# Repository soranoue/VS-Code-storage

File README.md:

# soranoue的暂存仓库

## 仓库介绍
    本仓库主要用于存放作者soranoue的部分学习代码,同时会用于测试学习
    有想要的代码可以自行取用(能帮忙Star下最好)

    目前包含的内容有:
    - 简单的README文件
    - 简单的C语言程序
    - 简单的Cpp程序(基于大学教材课后题)
    - 新建的Python文件夹(学习Python用)

    日后可能加入的内容有:
    - 8051内核单片机程序
    - ARM内核单片机程序
    - Altera FPGA CPLD
    - Xilinx FPGA SOC

## 关于作者
    soranoue,电子爱好者,偶尔也会捣鼓一些复古设备
    名称来源于日语'空の上'
    目前没有考取任何证书
    2022年起就读于中北大学(上兰帝国理工大学)(bushi)

#### 此README.md写于2025/3/15,测试用

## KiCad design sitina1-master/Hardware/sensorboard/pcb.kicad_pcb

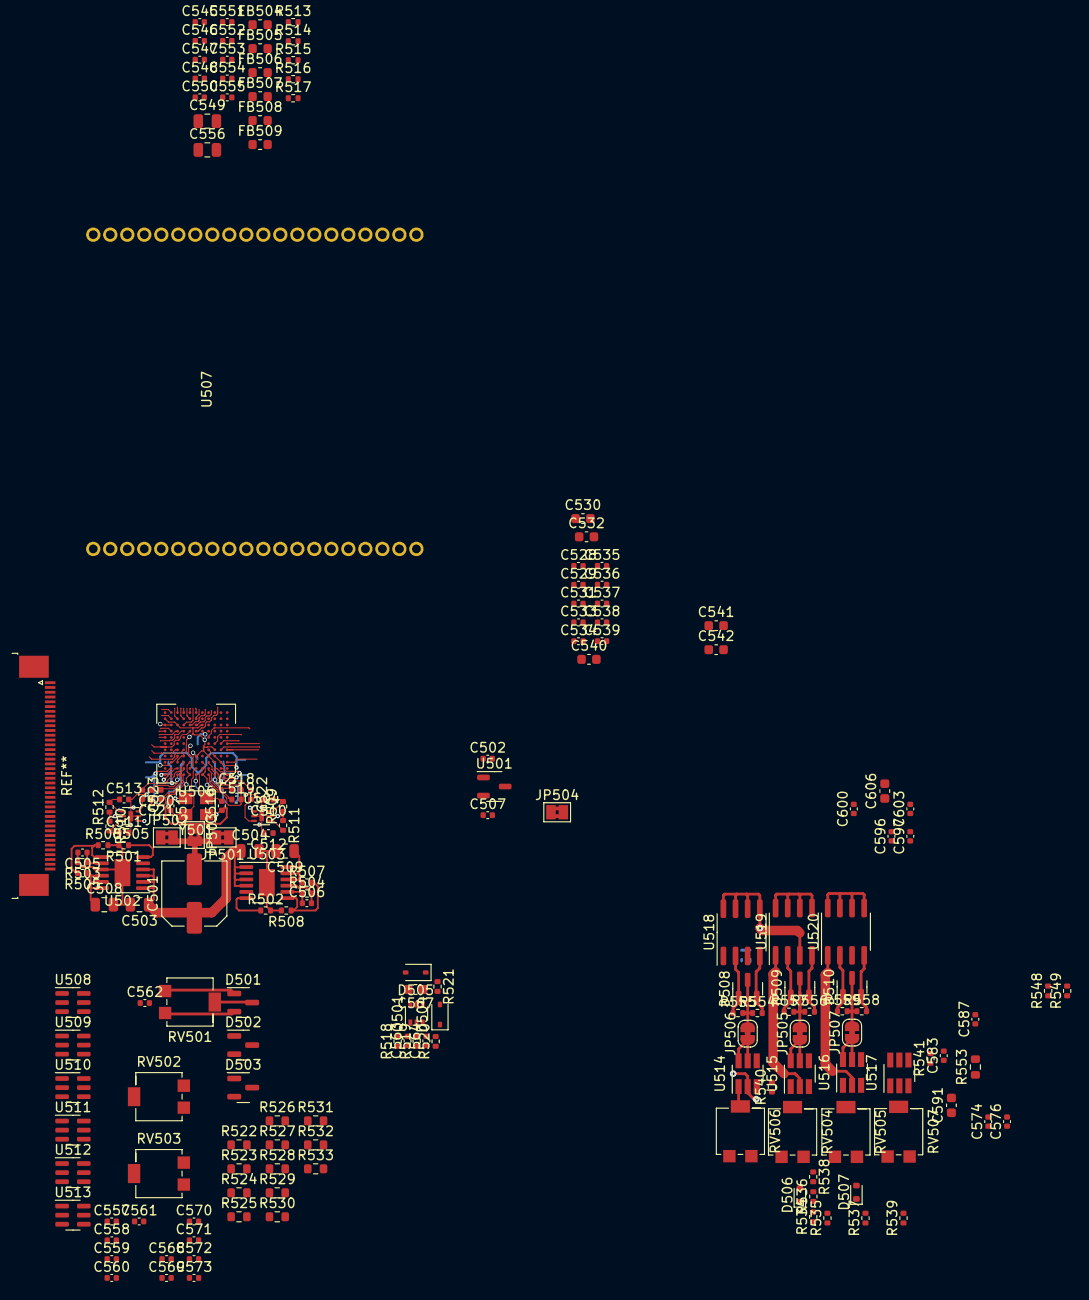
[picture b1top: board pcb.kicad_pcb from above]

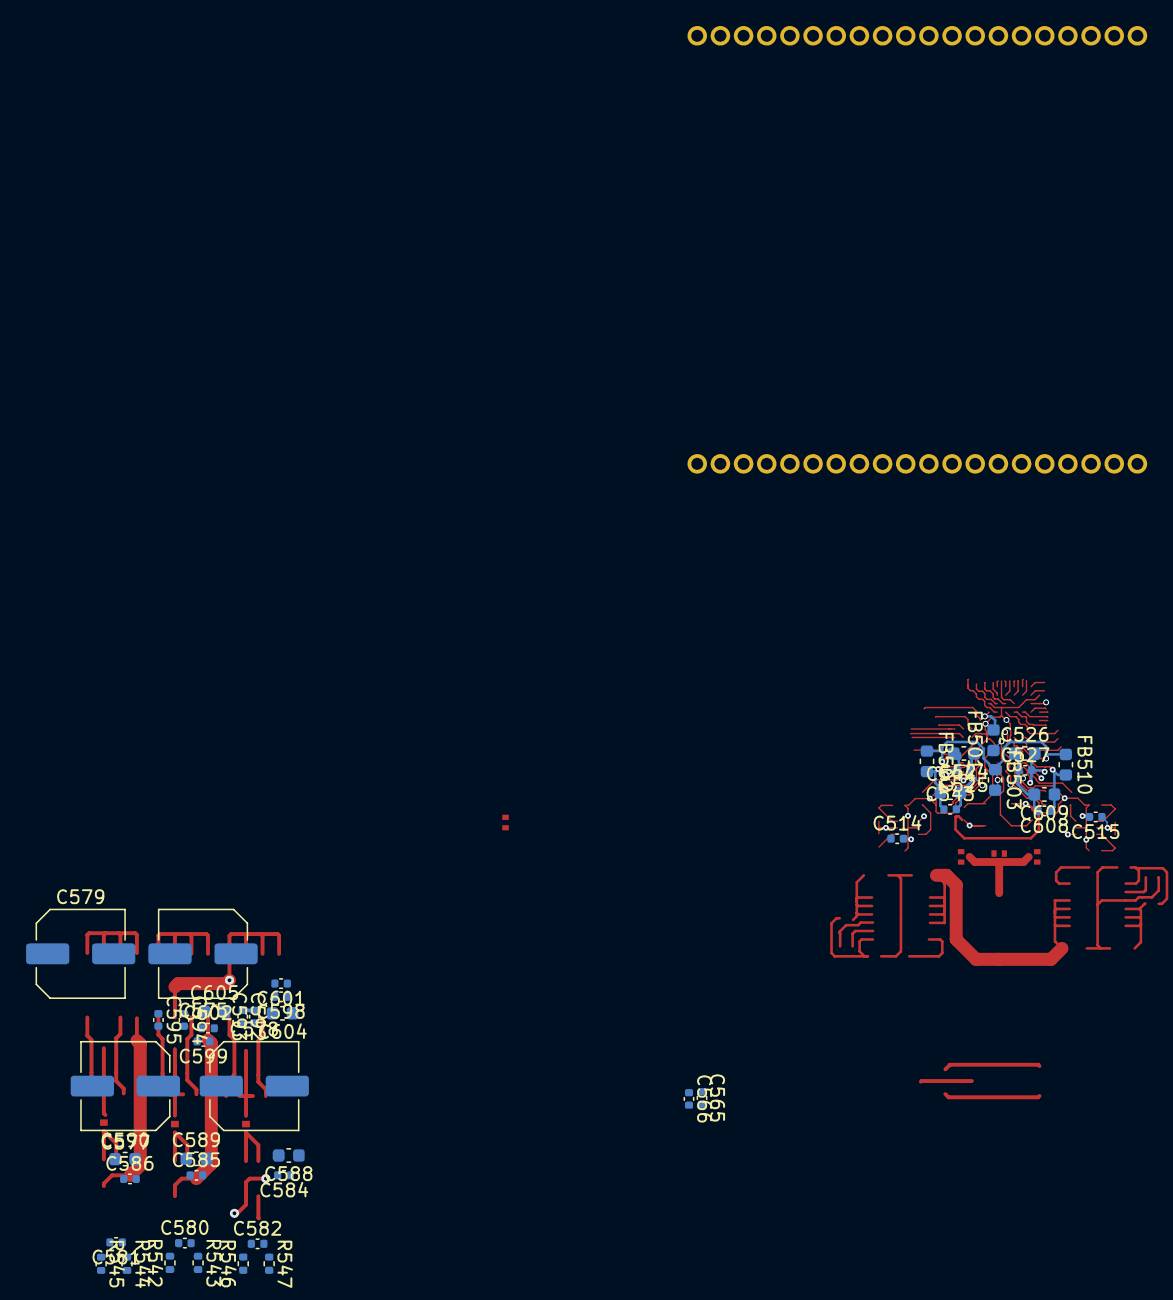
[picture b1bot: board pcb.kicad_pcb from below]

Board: 4 copper layers, 220 parts (45 on the bottom side), 129 nets.

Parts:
C501, C575, C577, C578, C579: 470uF; C_Elec_6.3x7.7
C502, C507, C518, C519, C520, C521, C574, C576, C601, C602, C603: 1uF; C_0402_1005Metric
C503, C504: 10uF; C_0805_2012Metric
C505, C506, C547, C548: 4.7uF; C_0402_1005Metric
C508, C509, C549, C556: 22uF 25V; C_0805_2012Metric
C510, C511, C512, C513, C514, C515, C522, C523, C525, C527, C528, C529, C531, C533, C534, C535, C536, C537, C538, C539, C543, C545, C546, C550, C551, C552, C553, C554, C555, C560, C561, C562, C563, C564, C565, C566, C568, C569, C570, C571, C572, C573, C580, C581, C582, C583, C584, C585, C586, C587, C598, C599, C600, C608: 100nF; C_0402_1005Metric
C516, C517: 18pF; C_0402_1005Metric
C524, C526, C530, C532, C540, C542, C544, C588, C589, C590, C591, C604, C605, C606, C609: 10uF; C_0603_1608Metric
C541: 100nF; C_0603_1608Metric
C557, C558, C559: 10uF; C_0402_1005Metric
C567: 1uF 25V; C_0603_1608Metric
C592, C593, C594, C595, C596, C597: 1nF; C_0402_1005Metric
D501, D502, D503, D508, D509, D510: BAT54S; SOT-23
D504, D505: B0540W; D_SOD-323
D506, D507: 1N4148; D_SOD-523
FB501, FB502, FB503, FB504, FB505, FB506, FB507, FB508, FB509, FB510: FerriteBead; L_0603_1608Metric
JP501, JP502, JP503, JP504: SolderJumper_2_Bridged; SolderJumper-2_P1.3mm_Bridged2Bar_Pad1.0x1.5mm
JP505, JP506, JP507: Jumper_2_Bridged; SolderJumper-2_P1.3mm_Bridged_RoundedPad1.0x1.5mm
Q501: BC847BPN; SOT-363_SC-70-6
R501, R502: 249R; R_0402_1005Metric
R503, R504: 30.1K; R_0402_1005Metric
R505, R507, R516: 270K 1%; R_0402_1005Metric
R506, R508: 22K 1%; R_0402_1005Metric
R509, R510: 49.9K 1%; R_0402_1005Metric
R511, R512, R513: 200K 1%; R_0402_1005Metric
R514: 120K 1%; R_0402_1005Metric
R515: 82K 1%; R_0402_1005Metric
R517: 7.5; R_0402_1005Metric
R518, R519, R521: 10K; R_0402_1005Metric
R520: 0; R_0402_1005Metric
R522, R523, R524, R525, R526, R527, R528, R529, R530, R531, R532, R533: 0.1; R_0603_1608Metric
R534, R535, R540, R541: 22; R_0402_1005Metric
R536, R537, R538, R539, R542, R543, R544, R545, R546, R547, R548, R549: 5k; R_0402_1005Metric
R553: Short; R_0603_1608Metric
R554, R555, R556, R557, R558, R559: 220; R_0402_1005Metric
RV501, RV502, RV503: 50K; Potentiometer_Bourns_3214G_Horizontal
RV504, RV505, RV506, RV507: 10K; Potentiometer_Bourns_3214G_Horizontal
U501: XC6206P152MR; SOT-23-3
U502, U503: LT3045xMSE; MSOP-12-1EP_3x4mm_P0.65mm_EP1.65x2.85mm
U504, U505: ADA4800; DFN-6-1EP_1.6x1.6mm_P0.5mm_EP0.5x1.05mm
U506: AD9990; BGA-112_11x11_8.0x8.0mm
U507: KAI-1100x; KAI-1100X
U508, U509, U510, U511, U512, U513: 74HC2G17; SC-74-6_1.5x2.9mm_P0.95mm
U514, U515, U516, U517: 1EDN7550B; SOT-23-6_Handsoldering
U518, U519, U520: IRF9389/7309; SOIC-8_3.9x4.9mm_P1.27mm
Y501: 28MHz; Crystal_SMD_3225-4Pin_3.2x2.5mm

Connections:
+1V5: C558.2, C568.1, D502.2 (K), RV502.1, U508.5 (VCC)
+1V8: C507.1, C528.2, FB501.2, U501.2 (VO), U506.H5 (DVDD)
+2V: C569.1, C570.1, C571.1, C572.1, C573.1, D501.2 (K), D503.2 (K), RV501.1, RV503.1, U509.5 (VCC), U510.5 (VCC), U511.5 (VCC), U512.5 (VCC), U513.5 (VCC)
+3V3: C502.1, C530.2, C531.2, C532.2, C533.2, C534.2, C535.2, C536.2, C537.2, C538.2, C539.2, C540.2, C559.2, C574.2, FB502.1, FB503.1, FB510.1, R546.2, R548.2, U501.3 (VI), U506.C2 (RGVDD_A), U506.C10 (RGVDD_B), U506.D3 (HVDD_A), U506.D9 (HVDD_B), U506.E4 (XVVDD), U506.J10 (DRVDD), U506.J11 (IOVDD)
+5V: C579.1, C587.2, C591.2, U517.4 (VDD)
+8V: C578.1, C584.2, C588.2, C598.2, C601.2, C604.2, U514.4 (VDD), U518.3 (SP)
+15VL: C508.1, C515.1, C546.1, FB504.1, R505.1, R510.1, R512.1, R515.1, U502.10 (OUTS), U502.11 (OUT), U502.12 (OUT), U505.5 (VCC)
+15VR: C509.1, C514.1, FB509.1, R507.1, R509.1, R511.1, U503.10 (OUTS), U503.11 (OUT), U503.12 (OUT), U504.5 (VCC)
+16V: C501.1, C503.1, C504.1, C565.2, Q501.4 (E2), R518.1, U502.1 (IN), U502.2 (IN), U502.3 (IN), U502.4 (EN/UV), U503.1 (IN), U503.2 (IN), U503.3 (IN), U503.4 (EN/UV)
-3V5: C557.1, C568.2, D502.1 (A), RV502.3, U508.2 (GND)
-4V: C545.2, C569.2, C570.2, C571.2, C572.2, C573.2, C576.1, C580.1, C581.1, D501.1 (A), D503.1 (A), R514.2, R543.1, R545.1, RV501.3, RV503.3, U509.2 (GND), U510.2 (GND), U511.2 (GND), U512.2 (GND), U513.2 (GND)
-9V: C575.2, C577.2, C585.1, C586.1, C587.1, C589.1, C590.1, C591.1, C599.2, C600.2, C602.1, C603.1, C605.1, C606.1, R517.1, R538.1, R539.1, U515.2 (GND), U516.2 (GND), U517.2 (GND), U519.1 (SN), U520.1 (SN)
-15V: C566.1, D504.2 (A), R520.2
/afe/AVDDA: C524.2, C525.2, U506.A1 (LDOOUT_A), U506.C4 (AVDD_A)
/afe/AVDDB: C526.2, C527.2, U506.A11 (LDOOUT_B), U506.C8 (AVDD_B)
/afe/AVSS: C516.1, C517.1, C541.2, C542.2, JP503.1 (A), U506.B3 (LDOVSS_A), U506.B9 (LDOVSS_B), Y501.2, Y501.4
/afe/AVSSA: C510.2, C512.2, C514.2, C518.2, C519.2, C524.1, C525.1, C543.2, C544.2, JP501.1 (A), U504.2 (VEE), U504.7 (EPAD), U506.A3 (AVSS_A), U506.A5 (AVSS_A), U506.C5 (AVSS_A)
/afe/AVSSB: C511.2, C513.2, C515.2, C520.2, C521.2, C526.1, C527.1, C608.2, C609.2, JP502.1 (A), U505.2 (VEE), U505.7 (EPAD), U506.A7 (AVSS_B), U506.A9 (AVSS_B), U506.C7 (AVSS_B)
/afe/CLI: C516.2, U506.B5 (CLI), Y501.1
/afe/CLO: C517.2, U506.B6 (CLO), Y501.3
/afe/DVSS: C528.1, C529.1, C530.1, C531.1, C532.1, C533.1, C534.1, C535.1, C536.1, C537.1, C538.1, C539.1, C540.1, JP504.1 (A), U506.C3 (RGVSS_A), U506.C6 (TCVSS), U506.C9 (RGVSS_B), U506.D4 (HVSS_A), U506.D6 (TCVSS), U506.D8 (HVSS_B), U506.E3 (XVVSS), U506.J5 (DVSS), U506.J9 (DRVSS), U506.K11 (IOVSS)
/ccd/VDDL: C549.1, C552.1, FB504.2, U507.3 (VDDL)
/ccd/VDDR: C555.1, C556.1, FB509.2, U507.18 (VDDR)
/ccd/VOD: C547.2, FB505.1, FB506.1, R513.2, R514.1
/ccd/VOGL: C553.1, FB506.2, U507.40 (OGL)
/ccd/VOGR: C554.1, FB505.2, U507.21 (OGR)
/ccd/VRDL: C550.1, FB508.2, U507.38 (VRDL)
/ccd/VRDR: C551.1, FB507.2, U507.23 (VRDR)
/ccd_driver/H1BINL: R524.1, U509.6 (1Y)
/ccd_driver/H1BINR: R525.1, U509.4 (2Y)
/ccd_driver/H1BL: R528.1, U511.6 (1Y)
/ccd_driver/H1BR: R531.1, U512.4 (2Y)
/ccd_driver/H1S: C561.2, D503.3 (COM), RV503.2, U509.1 (1A), U509.3 (2A), U511.1 (1A), U512.3 (2A), U513.1 (1A)
/ccd_driver/H1SL: R527.1, U510.4 (2Y)
/ccd_driver/H1SR: R532.1, U513.6 (1Y)
/ccd_driver/H2BL: R529.1, U511.4 (2Y)
/ccd_driver/H2BR: R530.1, U512.6 (1Y)
/ccd_driver/H2S: C562.2, D501.3 (COM), RV501.2, U510.1 (1A), U510.3 (2A), U511.3 (2A), U512.1 (1A), U513.3 (2A)
/ccd_driver/H2SL: R526.1, U510.6 (1Y)
/ccd_driver/H2SR: R533.1, U513.4 (2Y)
/ccd_driver/RGS: C560.2, D502.3 (COM), RV502.2, U508.1 (1A), U508.3 (2A)
/ccd_driver/RL: R522.1, U508.6 (1Y)
/ccd_driver/RR: R523.1, U508.4 (2Y)
/ccd_driver_v/V2S: D509.3 (COM), D510.3 (COM), JP505.2 (B), JP507.2 (B), R556.1, R557.2, R558.1, R559.2
/ccd_driver_v/V23: D508.3 (COM), JP506.2 (B), R554.1, R555.2
AFE_FDG: R541.1, U506.G4 (XV4)
AFE_H1: C561.1, U506.E1 (H1A)
AFE_H2: C562.1, U506.E2 (H2A)
AFE_RG: C560.1, U506.C1 (HL_A)
AFE_STROBE: C563.2, C564.2, U506.G11 (GPO1)
AFE_V1: R535.1, U506.F3 (XV1)
AFE_V2: R534.1, U506.F2 (XV2)
AFE_V23: R540.1, U506.F1 (XV3)
CCDIN_L: U505.1 (IN), U507.2 (VOUTL)
CCDIN_R: U504.1 (IN), U507.19 (VOUTR)
FDG_CCD: R553.1, U507.22 (FD), U507.39 (FD)
GND: C501.2, C502.2, C503.2, C504.2, C505.2, C506.2, C507.2, C508.2, C509.2, C545.1, C546.2, C547.1, C548.2, C549.2, C550.2, C551.2, C552.2, C553.2, C554.2, C555.2, C556.2, C557.2, C558.1, C559.1, C565.1, C566.2, C574.1, C575.1, C576.2, C577.1, C578.2, C579.2, C582.1, C583.1, C584.1, C585.2, C586.2, C588.1, C589.2, C590.2, C598.1, C599.1, C600.1, C601.1, C602.2, C603.2, C604.1, C605.2, C606.2, D506.2 (A), D507.2 (A), JP501.2 (B), JP502.2 (B), JP503.2 (B), JP504.2 (B), R501.2, R502.2, R503.2, R504.2, R506.2, R508.2, R513.1, R516.2, R519.2, R521.2, R542.2, R544.2, R547.1, R549.1, U501.1 (GND), U502.9 (GND), U502.13 (GND), U503.9 (GND), U503.13 (GND), U507.4 (GND), U507.6 (GND), U507.15 (GND), U507.17 (GND), U507.26 (GND), U507.28 (GND), U507.29 (GND), U507.30 (GND), U507.31 (GND), U507.32 (GND), U507.33 (GND), U507.35 (GND), U514.2 (GND), U515.4 (VDD), U516.4 (VDD), U518.1 (SN), U520.3 (SP)
H1BINL_CCD: R524.2, U507.5 (H1BINL)
H1BINR_CCD: R525.2, U507.16 (H1BINR)
H1BL_CCD: R528.2, U507.9 (H1BL)
H1BR_CCD: R531.2, U507.12 (H1BR)
H1SL_CCD: R527.2, U507.8 (H1SL)
H1SR_CCD: R532.2, U507.13 (H1SR)
H2BL_CCD: R529.2, U507.10 (H2BL)
H2BR_CCD: R530.2, U507.11 (H2BR)
H2SL_CCD: R526.2, U507.7 (H2SL)
H2SR_CCD: R533.2, U507.14 (H2SR)
unnamed: C548.1, FB507.1, FB508.1, R515.2, R516.1
unnamed: C564.1, D504.1 (K), Q501.2 (B1), R519.1
unnamed: D506.1 (K), R534.2, R536.1
unnamed: D507.1 (K), R535.2, R537.1
unnamed: C593.1, D508.1 (A), R555.1, U518.2 (GN)
unnamed: C592.2, D508.2 (K), R554.2, U518.4 (GP)
unnamed: C595.1, D509.1 (A), R557.1, U519.2 (GN)
unnamed: C594.2, D509.2 (K), R556.2, U519.4 (GP)
unnamed: C597.1, D510.1 (A), R559.1, U520.2 (GN)
unnamed: C596.2, D510.2 (K), R558.2, U520.4 (GP)
unnamed: JP505.1 (A), U515.5 (OUT_SRC), U515.6 (OUT_SNK)
unnamed: JP506.1 (A), U514.5 (OUT_SRC), U514.6 (OUT_SNK)
unnamed: JP507.1 (A), U516.5 (OUT_SRC), U516.6 (OUT_SNK)
unnamed: C567.2, Q501.3 (C2), Q501.6 (C1)
unnamed: Q501.1 (E1), R520.1
unnamed: C563.1, Q501.5 (B2), R518.2
unnamed: R542.1, RV504.1
unnamed: R543.2, RV504.3
unnamed: R544.1, RV505.1
unnamed: R545.2, RV505.3
unnamed: R546.1, RV506.1
unnamed: R547.2, RV506.3
unnamed: R548.1, RV507.1
unnamed: R549.2, RV507.3
unnamed: R501.1, U502.6 (ILIM)
unnamed: R505.2, R506.1, U502.7 (PGFB)
unnamed: C505.1, R503.1, U502.8 (SET)
unnamed: R502.1, U503.6 (ILIM)
unnamed: R507.2, R508.1, U503.7 (PGFB)
unnamed: C506.1, R504.1, U503.8 (SET)
unnamed: C512.1, R511.2, U504.4 (IDRV)
unnamed: C510.1, R509.2, U504.6 (ISF)
unnamed: C522.2, U504.3 (OUT)
unnamed: C513.1, R512.2, U505.4 (IDRV)
unnamed: C511.1, R510.2, U505.6 (ISF)
unnamed: C523.2, U505.3 (OUT)
unnamed: C522.1, U506.A2 (CCDIN_A)
unnamed: C523.1, U506.A10 (CCDIN_B)
unnamed: C541.1, C542.1, FB503.2, U506.A6 (CLIVDD)
unnamed: C543.1, C544.1, FB502.2, U506.B2 (LDOIN_A)
unnamed: C608.1, C609.1, FB510.2, U506.B10 (LDOIN_B)
unnamed: C519.1, U506.A4 (REFB_A)
unnamed: C521.1, U506.A8 (REFB_B)
unnamed: C518.1, U506.B4 (REFT_A)
unnamed: C520.1, U506.B8 (REFT_B)
unnamed: C529.2, FB501.1, U506.B7 (TCVDD)
unnamed: R517.2, U507.27 (ESD)
unnamed: R540.2, U514.3 (IN+)
unnamed: C582.2, RV506.2, U514.1 (IN-)
unnamed: R536.2, R538.2, U515.3 (IN+)
unnamed: C580.2, RV504.2, U515.1 (IN-)
unnamed: R537.2, R539.2, U516.3 (IN+)
unnamed: C581.2, RV505.2, U516.1 (IN-)
unnamed: R541.2, U517.3 (IN+)
unnamed: C583.2, RV507.2, U517.1 (IN-)
unnamed: R553.2, U517.5 (OUT_SRC), U517.6 (OUT_SNK)
unnamed: C592.1, C593.2, U518.5 (DP), U518.6 (DP), U518.7 (DN), U518.8 (DN), U519.3 (SP)
RL_CCD: R522.2, U507.1 (RL)
RR_CCD: R523.2, U507.20 (RR)
V1_CCD: C596.1, C597.2, U507.25 (V1), U507.37 (V1), U520.5 (DP), U520.6 (DP), U520.7 (DN), U520.8 (DN)
V2_CCD: C594.1, C595.2, U507.24 (V2), U507.36 (V2), U519.5 (DP), U519.6 (DP), U519.7 (DN), U519.8 (DN)
VSUB_CCD: C567.1, D505.1 (K), R521.1, U507.34 (SUB)

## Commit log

2023-09-05 new file: C/output/test.exe new file: C/test.c new file: CPP/output/test.exe new file: CPP/test.cpp new file: Py/seletest.py new file: "Py/\344\271\220\350\267\221.py" new file: "Py/\350\257\210\351\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
2023-09-05 renamed: "Py/\344\271\220\350\267\221.py" -> Py/lepao.py renamed: "Py/\350\257\210\351\252\227\346\265\213\345\216\213.py" -> Py/zhapianceya.py
2023-09-05 new file: Py/test.py
2023-09-05 new file: C/load.c new file: C/output/load.exe
2023-09-05 modified: C/output/load.exe
2023-09-05 new file: C/enigma.c new file: C/output/enigma.exe modified: C/output/load.exe new file: C/output/rand.exe new file: C/rand.c
2023-09-06 new file: CPP/enigma(sourse).cpp
2023-09-07 new file: CPP/CSCI2270_FinalProject-master/Driver new file: CPP/CSCI2270_FinalProject-master/Driver.cpp new file: CPP/CSCI2270_FinalProject-master/Driver.exe new file: CPP/CSCI2270_FinalProject-maste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
2023-09-07 new file: CPP/output/enigma(sourse).exe
2023-09-11 modified: Py/seletest.py new file: Py/webdriver/geckodriver.exe new file: Py/webdriver/msedgedriver.exe
2023-09-11 modified: Py/zhapianceya.py
2023-09-22 new file: .vscode/settings.json
    new file: .vscode/settings.json
2024-03-15 new file: C/SBUS_test.c new file: C/bmp_compress.c new file: C/output/SBUS_test.exe new file: C/output/bmp_compress.exe modified: C/output/test.exe modified: C/test.c new file: CPP/MonkeySort.cpp new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
2024-03-15 modified: C/test.c
2024-06-03 new file: .vscode/c_cpp_properties.json new file: .vscode/launch.json new file: .vscode/tasks.json new file: C/output/sha256.exe new file: C/sha256.c
2024-06-06 modified: .vscode/c_cpp_properties.json new file: C/output/rsa.exe modified: C/output/test.exe new file: C/rsa.c new file: C/text.txt
2024-06-07 modified: C/output/rsa.exe modified: C/output/sha256.exe modified: C/sha256.c
2024-06-07 modified: C/output/rsa.exe modified: C/rsa.c
2024-06-07 modified: C/output/rsa.exe
2024-06-07 new file: C/encoded.rsa modified: C/output/rsa.exe modified: C/rsa.c
2024-06-07 modified: C/encoded.rsa new file: C/huffman_decode.c new file: C/huffman_encode.c new file: C/output/huffman_decode.exe new file: C/output/huffman_encode.exe modified: C/output/rsa.exe new file: C/te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
2024-06-08 modified: C/encoded.rsa new file: C/lena.bmp modified: C/output/rsa.exe modified: C/output/sha256.exe new file: C/output/snake.exe modified: C/rsa.c new file: C/snake.c deleted: C/text.huf new file: 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
2025-03-15 文件更改
2025-03-15 添加README文件

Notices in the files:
sitina1-master/Hardware/sensorboard/pcb.kicad_pcb:
Copyright 2022 Wenting Zhang
This source describes Open Hardware and is licensed under the CERN-OHL-S v2.
